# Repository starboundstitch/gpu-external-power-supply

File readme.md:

# GPU External Power Supply

The GPU External Power Supply is a project that aims to replace any computer graphics cards' power delivery system with a completely custom board. This repository contains all code, firmware, and schematics required to build the card as well as documentation on how it works.

The sister repository [geps-app](https://github.com/starboundstitch/geps-app) contains the code for the GUI application.

## Summary

The External GPU Power Card is a designed to seamlessly integrate with existing GPUs. It works by replacing the Vcore and Vmem rails with new power stages that have reduced noise, an increased voltage range, and an increased maximum current which should provide additional stability and performance benefits.

The power supply also allows full control of its voltage characteristics to provide unlimited overclocking potential. The device integrates with our companion application to provide real time monitoring and adjustment using a GUI interface, allowing more informed decisions in the overclocking process to extract as much performance as possible.

<div align="center""> 
Prototype 2
</div>

<div align="center""> 
Prototype 2 is attached to a gtx 580
</div>

## Specs

* 12 Phases (10+2)
* Vcore
  * 0-2V
  * 500A Tested
  * 900A Theoretical
  * 10 Phases
* Vcore
  * 0-2.3V
  * 100A Tested
  * 180A Theoretical
  * 2 Phases

## Hardware

This section contains the KICAD project and all the associated files.

We make extensive use of hierarchy in this project and have the following schematics:
* Vcore_stage
  * Single MOSFET that connects to the VRM Controller Vcore Channel
* Vmem_stage
  * Single MOSFET that connects to the VRM Controller Vmem Channel
* VRM_Controller
  * VRM Controller with required pinouts and filtering
* 12V_Supply
  * Input filtering and connectors
* Low_Current_Supply
  * 3.3V & 5V buck converters and LED status
* Onboard_Control
  * Buttons and Display
* U_Controller
  * Microcontroller and required connectors (including USB-C)

## Firmware

This section contains all micro-controller code and is using the rust language with the [stmf4XX-hal](https://github.com/stm32-rs/stm32f4xx-hal) library.

> [!CAUTION]
> The stm32f401RE that is used does NOT have enough SRAM to run in debug mode and it will NOT flash.

The controller should automatically build and flash with:

```
cargo run --release
```

Additionally, in the future we will support flashing via USB DFU mode (instructions TBD).

## License

All the code and hardware files in this repository are licensed according to the GPLv3 in the [LICENSE](https://github.com/starboundstitch/gpu-external-power-supply/blob/master/LICENSE) file.

In addition, many of the symbols and footprints are provided by the manufacturers for use and are thus liable under the manufactures' licenses.

This project was created by [@Xunnin](https://github.com/Xunnin), [@starboundstitch](https://github.com/starboundstitch), and [@StefClef](https://github.com/StefClef).

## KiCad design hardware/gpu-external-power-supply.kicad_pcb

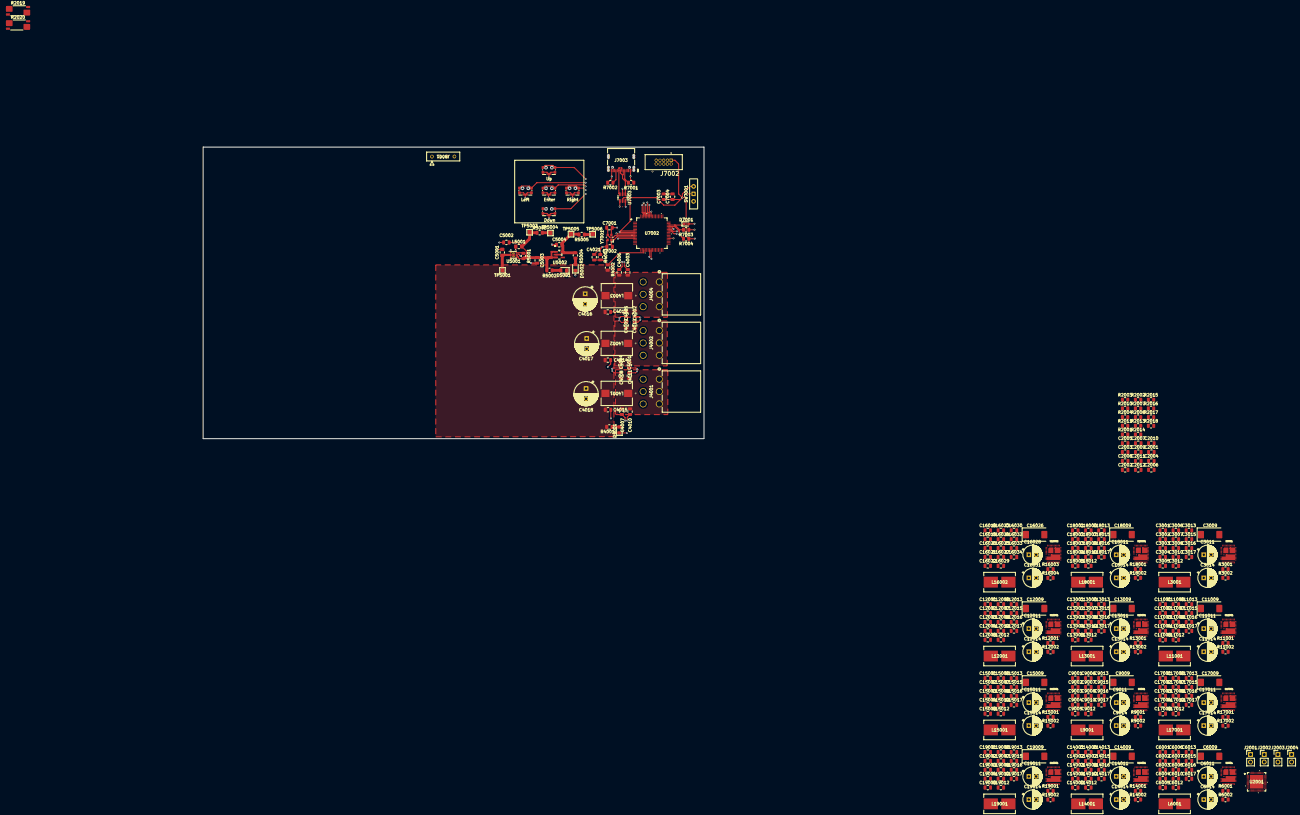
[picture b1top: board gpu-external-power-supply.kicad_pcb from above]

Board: 6 copper layers, 170.2 x 99.1 mm, 354 parts (0 on the bottom side), 141 nets.

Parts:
C2001, C2004: 1nF; C_0805_2012Metric
C2002, C2010, C2011, C2012, C5003, C5004: 1uF; C_0805_2012Metric
C2003, C2005: 100pF; C_0805_2012Metric
C2006, C3003, C3006, C3007, C3017, C6003, C6006, C6007, C6017, C9003, C9006, C9007, C9017, C11003, C11006, C11007, C11017, C12003, C12006, C12007, C12017, C13003, C13006, C13007, C13017, C14003, C14006, C14007, C14017, C15003, C15006, C15007, C15017, C16020, C16023, C16024, C16034, C17003, C17006, C17007, C17017, C18003, C18006, C18007, C18017, C19003, C19006, C19007, C19017: 0.1uF; C_0805_2012Metric
C2007, C3016, C6016, C9016, C11016, C12016, C13016, C14016, C15016, C16033, C17016, C18016, C19016: 4.7uF; C_0805_2012Metric
C2008, C2009: 2200pF; C_0805_2012Metric
C3001, C3005, C6001, C6005, C9001, C9005, C11001, C11005, C12001, C12005, C13001, C13005, C14001, C14005, C15001, C15005, C16018, C16022, C17001, C17005, C18001, C18005, C19001, C19005: 47pF; C_0805_2012Metric
C3002, C3004, C6002, C6004, C9002, C9004, C11002, C11004, C12002, C12004, C13002, C13004, C14002, C14004, C15002, C15004, C16019, C16021, C17002, C17004, C18002, C18004, C19002, C19004: 2.2uF; C_0805_2012Metric
C3008, C3010, C3012, C3015, C5002, C6008, C6010, C6012, C6015, C9008, C9010, C9012, C9015, C11008, C11010, C11012, C11015, C12008, C12010, C12012, C12015, C13008, C13010, C13012, C13015, C14008, C14010, C14012, C14015, C15008, C15010, C15012, C15015, C16025, C16027, C16029, C16032, C17008, C17010, C17012, C17015, C18008, C18010, C18012, C18015, C19008, C19010, C19012, C19015: 22uF; C_0805_2012Metric
C3009, C6009, C9009, C11009, C12009, C13009, C14009, C15009, C16026, C17009, C18009, C19009: 470uF; CP_EIA-7343-40_Kemet-Y
C3011, C3014, C6011, C6014, C9011, C9014, C11011, C11014, C12011, C12014, C13011, C13014, C14011, C14014, C15011, C15014, C16028, C16031, C17011, C17014, C18011, C18014, C19011, C19014: 220uF; CP_Radial_D6.3mm_P2.50mm
C3013, C6013, C9013, C11013, C12013, C13013, C14013, C15013, C16030, C17013, C18013, C19013: 47uF; C_0805_2012Metric
C4001, C4002, C4003: 470u; C_0805_2012Metric
C4004, C4005, C4006: 47u; C_0805_2012Metric
C4007, C4008, C4009: 10u; C_0805_2012Metric
C4010, C4011, C4012, C4021: 0.1u; C_0805_2012Metric
C4013, C4014, C4015: 330u; C_0805_2012Metric
C4016, C4017, C4018: 470u; CP_Radial_D8.0mm_P3.50mm
C5001: 10uF; C_0805_2012Metric_Pad1.18x1.45mm_HandSolder
C7001, C7002: 6pF; C_0805_2012Metric
C7003: 4.7u; C_0805_2012Metric
C7004: 100n; C_0805_2012Metric
D4001, D5001, D5002: 150080SS75000; LED_0805_2012Metric_Pad1.15x1.40mm_HandSolder
D7001: GG060303100N2P; D_0603_1608Metric
J2001, J2002, J2003, J2004: Conn_01x02_Pin; PinHeader_1x02_P2.54mm_Vertical
J4001, J4002, J4004: 353180620; CONN_35318-06xx_MOL
J7002: Conn_ARM_JTAG_SWD_10; CNC_3221-10-0100-00
J7003: USB_C_Receptacle_USB2.0_16P; 12402012E212A_AMP
J8001: Conn_01x04_Pin; CONN_PPTC041LFBN-RC_SUL
L3001, L6001, L9001, L11001, L12001, L13001, L14001, L15001, L16002, L17001, L18001, L19001: 150nH; IND_IHVR-4025JZ-3Z_VIS
L4001, L4002, L4003: 170nH; IND_IFLR4031GCERR17M01_VIS-L
L5001: 2.2uH; L_0805_2012Metric_Pad1.15x1.40mm_HandSolder
R2001, R2002, R2007, R2008, R2013, R2014, R2015, R2016, R2017, R2018, R4002: 10k; R_0805_2012Metric
R2003: 130k; R_0805_2012Metric
R2004, R2011: 37.4k; R_0805_2012Metric
R2010: 2430k; R_0805_2012Metric
R2019, R2020: 1m; R_Shunt_Vishay_WSK2512_6332Metric_T1.19mm
R3001, R6001, R9001, R11001, R12001, R13001, R14001, R15001, R16003, R17001, R18001, R19001: 2.2; R_0805_2012Metric
R3002, R6002, R9002, R11002, R12002, R13002, R14002, R15002, R16004, R17002, R18002, R19002: 0; R_0805_2012Metric
R4001: 337; R_0805_2012Metric
R4003: 3.5k; R_0805_2012Metric
R5001, R7004: 100k; R_0805_2012Metric
R5002: 100+-5; R_0805_2012Metric
R5003, R5005: 1; R_0805_2012Metric
R5004: 45+-5; R_0805_2012Metric
R7001, R7002: 5K1; R_0805_2012Metric
R7003: 10K; R_0805_2012Metric
SW7001: SW_Wuerth_450301014042; SW_Slide-03_Wuerth-WS-SLTV_10x2.5x6.4_P2.54mm
SW8001, SW8002, SW8003, SW8004, SW8005: CK_KMS2xxG; SW_SPST_CK_KMS2xxGP
TP5001: 12V -> 5V; TestPoint_Pad_1.5x1.5mm
TP5003, TP5004, TP5005, TP5006: TestPoint; TestPoint_Pad_1.5x1.5mm
U2001: TPS536C7B1RSLT; QFN48_6X6_TEX
U3001, U6001, U9001, U11001, U12001, U13001, U14001, U15001, U16002, U17001, U18001, U19001: AOZ5276QI
U5001: TPS62160DSG; WSON-8-1EP_2x2mm_P0.5mm_EP0.9x1.6mm_ThermalVias
U5002: TPS73633DBVR; DBV5
U7002: STM32C071RBT6; LQFP-64_STM
U7003: USBLC6-2SC6; SOT-23-6
Y7001: Crystal_GND24; Crystal_SMD_Abracon_ABM10-4Pin_2.5x2.0mm

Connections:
3.3V: C2006.1, C2007.1, C7003.1, C7004.1, J7002.1 (VTref), J8001.2, R2001.1, R2007.1, R2013.1, R2014.1, R2015.1, R2016.1, R2017.1, R2018.1, R5005.2, R7004.1, SW7001.3 (A), TP5006.1, U2001.47 (VCC), U7002.7 (VREF+), U7002.8 (VDD/VDDA), U7003.5 (VBUS)
5V: R5003.2, TP5004.1
12V: C4013.1, C4014.1, C4015.1, C4016.1, C4017.1, C4018.1, C5001.1, L4001.2, L4002.2, L4003.2, R4001.1, R4002.1, TP5001.1, U5001.2 (VIN), U5001.3 (EN)
12V_VOL_SENS: C4021.1, R4002.2, R4003.1, U7002.19 (PA2)
/5v: C3002.1, C6002.1, C9002.1, C11002.1, C12002.1, C13002.1, C14002.1, C15002.1, C16019.1, C17002.1, C18002.1, C19002.1, R3001.1, R6001.1, R9001.1, R11001.1, R12001.1, R13001.1, R14001.1, R15001.1, R16003.1, R17001.1, R18001.1, R19001.1, U3001.4 (PVCC), U3001.35 (EN), U6001.4 (PVCC), U6001.35 (EN), U9001.4 (PVCC), U9001.35 (EN), U11001.4 (PVCC), U11001.35 (EN), U12001.4 (PVCC), U12001.35 (EN), U13001.4 (PVCC), U13001.35 (EN), U14001.4 (PVCC), U14001.35 (EN), U15001.4 (PVCC), U15001.35 (EN), U16002.4 (PVCC), U16002.35 (EN), U17001.4 (PVCC), U17001.35 (EN), U18001.4 (PVCC), U18001.35 (EN), U19001.4 (PVCC), U19001.35 (EN)
/U Controller/PF0: C7001.2, U7002.10 (PF0-OSC_IN), Y7001.3
/U Controller/PF1: C7002.2, U7002.11 (PF1-OSC_OUT), Y7001.1
/VRM Controller/ADDR_CONFIG: R2010.2, R2011.1, U2001.42 (ADDR_CONFIG)
/VRM Controller/CSNIN: C2011.2, C2012.1, C3007.1, C3008.1, C3010.1, C3012.1, C3014.1, C6007.1, C6008.1, C6010.1, C6012.1, C6014.1, C9007.1, C9008.1, C9010.1, C9012.1, C9014.1, C11007.1, C11008.1, C11010.1, C11012.1, C11014.1, C12007.1, C12008.1, C12010.1, C12012.1, C12014.1, C13007.1, C13008.1, C13010.1, C13012.1, C13014.1, C14007.1, C14008.1, C14010.1, C14012.1, C14014.1, C15007.1, C15008.1, C15010.1, C15012.1, C15014.1, C16024.1, C16025.1, C16027.1, C16029.1, C16031.1, C17007.1, C17008.1, C17010.1, C17012.1, C17014.1, C18007.1, C18008.1, C18010.1, C18012.1, C18014.1, C19007.1, C19008.1, C19010.1, C19012.1, C19014.1, R2019.1, R2020.2, U2001.46 (VIN_CSNIN), U3001.25 (VIN), U3001.30 (VIN), U6001.25 (VIN), U6001.30 (VIN), U9001.25 (VIN), U9001.30 (VIN), U11001.25 (VIN), U11001.30 (VIN), U12001.25 (VIN), U12001.30 (VIN), U13001.25 (VIN), U13001.30 (VIN), U14001.25 (VIN), U14001.30 (VIN), U15001.25 (VIN), U15001.30 (VIN), U16002.25 (VIN), U16002.30 (VIN), U17001.25 (VIN), U17001.30 (VIN), U18001.25 (VIN), U18001.30 (VIN), U19001.25 (VIN), U19001.30 (VIN)
/VRM Controller/CSPIN: C2010.1, C2011.1, R2019.2, R2020.1, U2001.45 (CSPIN)
/VRM Controller/CUR_A_9: C18001.1, U2001.35 (ACSP9), U18001.38 (IMON)
/VRM Controller/Cur_A_1: C6001.1, U2001.27 (ACSP1), U6001.38 (IMON)
/VRM Controller/Cur_A_2: C11001.1, U2001.28 (ACSP2), U11001.38 (IMON)
/VRM Controller/Cur_A_3: C12001.1, U2001.29 (ACSP3), U12001.38 (IMON)
/VRM Controller/Cur_A_4: C13001.1, U2001.30 (ACSP4), U13001.38 (IMON)
/VRM Controller/Cur_A_5: C14001.1, U2001.31 (ACSP5), U14001.38 (IMON)
/VRM Controller/Cur_A_6: C15001.1, U2001.32 (ACSP6), U15001.38 (IMON)
/VRM Controller/Cur_A_7: C16018.1, U2001.33 (ACSP7), U16002.38 (IMON)
/VRM Controller/Cur_A_8: C17001.1, U2001.34 (ACSP8), U17001.38 (IMON)
/VRM Controller/Cur_A_10: C19001.1, U2001.36 (ACSP10), U19001.38 (IMON)
/VRM Controller/Cur_B_1: C3001.1, U2001.38 (BCSP1), U3001.38 (IMON)
/VRM Controller/Cur_B_2: C9001.1, U2001.37 (BCSP2), U9001.38 (IMON)
/VRM Controller/PWM_A_1: U2001.12 (APWM1), U6001.34 (PWM)
/VRM Controller/PWM_A_2: U2001.11 (APWM2), U11001.34 (PWM)
/VRM Controller/PWM_A_3: U2001.10 (APWM3), U12001.34 (PWM)
/VRM Controller/PWM_A_4: U2001.9 (APWM4), U13001.34 (PWM)
/VRM Controller/PWM_A_5: U2001.8 (APWM5), U14001.34 (PWM)
/VRM Controller/PWM_A_6: U2001.7 (APWM6), U15001.34 (PWM)
/VRM Controller/PWM_A_7: U2001.6 (APWM7), U16002.34 (PWM)
/VRM Controller/PWM_A_8: U2001.5 (APWM8), U17001.34 (PWM)
/VRM Controller/PWM_A_9: U2001.4 (APWM9), U18001.34 (PWM)
/VRM Controller/PWM_A_10: U2001.3 (APWM10), U19001.34 (PWM)
/VRM Controller/PWM_B_1: U2001.1 (BPWM1), U3001.34 (PWM)
/VRM Controller/PWM_B_2: U2001.2 (BPWM2), U9001.34 (PWM)
/VRM Controller/VBOOT_A: R2003.2, R2004.1, U2001.18 (VBOOT_CHA)
/VRM Controller/VREF: C2002.2, C3001.2, C3003.1, C6001.2, C6003.1, C9001.2, C9003.1, C11001.2, C11003.1, C12001.2, C12003.1, C13001.2, C13003.1, C14001.2, C14003.1, C15001.2, C15003.1, C16018.2, C16020.1, C17001.2, C17003.1, C18001.2, C18003.1, C19001.2, C19003.1, R2003.1, R2010.1, U2001.48 (VREF), U3001.39 (REFIN), U6001.39 (REFIN), U9001.39 (REFIN), U11001.39 (REFIN), U12001.39 (REFIN), U13001.39 (REFIN), U14001.39 (REFIN), U15001.39 (REFIN), U16002.39 (REFIN), U17001.39 (REFIN), U18001.39 (REFIN), U19001.39 (REFIN)
AVR_READY: R2015.2, U2001.16 (AVR_RDY), U7002.38 (PC6)
A_ENABLE: C2001.1, R2001.2, R2002.1, U2001.17 (AVR_EN), U7002.49 (PC9)
B_ENABLE: C2004.1, R2007.2, R2008.1, U2001.19 (BVR_EN_/_RESET#_/_SYNC), U7002.64 (PC10)
CORE_TEMO: C2009.1, U2001.43 (BTSEN_/_ATSEN_/_TSEN)
CORE_TEMP: C6005.1, C11005.1, C12005.1, C13005.1, C14005.1, C15005.1, C16022.1, C17005.1, C18005.1, C19005.1, U6001.36 (TMON), U11001.36 (TMON), U12001.36 (TMON), U13001.36 (TMON), U14001.36 (TMON), U15001.36 (TMON), U16002.36 (TMON), U17001.36 (TMON), U18001.36 (TMON), U19001.36 (TMON)
GND: C2001.2, C2002.1, C2004.2, C2006.2, C2007.2, C2008.2, C2009.2, C2010.2, C2012.2, C3002.2, C3003.2, C3004.2, C3005.2, C3007.2, C3008.2, C3009.2, C3010.2, C3011.2, C3012.2, C3013.2, C3014.2, C3015.2, C3016.2, C3017.2, C4001.2, C4002.2, C4003.2, C4004.2, C4005.2, C4006.2, C4007.2, C4008.2, C4009.2, C4010.2, C4011.2, C4012.2, C4013.2, C4014.2, C4015.2, C4016.2, C4017.2, C4018.2, C4021.2, C5001.2, C5002.2, C5003.2, C5004.2, C6002.2, C6003.2, C6004.2, C6005.2, C6007.2, C6008.2, C6009.2, C6010.2, C6011.2, C6012.2, C6013.2, C6014.2, C6015.2, C6016.2, C6017.2, C7001.1, C7002.1, C7003.2, C7004.2, C9002.2, C9003.2, C9004.2, C9005.2, C9007.2, C9008.2, C9009.2, C9010.2, C9011.2, C9012.2, C9013.2, C9014.2, C9015.2, C9016.2, C9017.2, C11002.2, C11003.2, C11004.2, C11005.2, C11007.2, C11008.2, C11009.2, C11010.2, C11011.2, C11012.2, C11013.2, C11014.2, C11015.2, C11016.2, C11017.2, C12002.2, C12003.2, C12004.2, C12005.2, C12007.2, C12008.2, C12009.2, C12010.2, C12011.2, C12012.2, C12013.2, C12014.2, C12015.2, C12016.2, C12017.2, C13002.2, C13003.2, C13004.2, C13005.2, C13007.2, C13008.2, C13009.2, C13010.2, C13011.2, C13012.2, C13013.2, C13014.2, C13015.2, C13016.2, C13017.2, C14002.2, C14003.2, C14004.2, C14005.2, C14007.2, C14008.2, C14009.2, C14010.2, C14011.2, C14012.2, C14013.2, C14014.2, C14015.2, C14016.2, C14017.2, C15002.2, C15003.2, C15004.2, C15005.2, C15007.2, C15008.2, C15009.2, C15010.2, C15011.2, C15012.2, C15013.2, C15014.2, C15015.2, C15016.2, C15017.2, C16019.2, C16020.2, C16021.2, C16022.2, C16024.2, C16025.2, C16026.2, C16027.2, C16028.2, C16029.2, C16030.2, C16031.2, C16032.2, C16033.2, C16034.2, C17002.2, C17003.2, C17004.2, C17005.2, C17007.2, C17008.2, C17009.2, C17010.2, C17011.2, C17012.2, C17013.2, C17014.2, C17015.2, C17016.2, C17017.2, C18002.2, C18003.2, C18004.2, C18005.2, C18007.2, C18008.2, C18009.2, C18010.2, C18011.2, C18012.2, C18013.2, C18014.2, C18015.2, C18016.2, C18017.2, C19002.2, C19003.2, C19004.2, C19005.2, C19007.2, C19008.2, C19009.2, C19010.2, C19011.2, C19012.2, C19013.2, C19014.2, C19015.2, C19016.2, C19017.2, D4001.1 (K), D5001.1 (K), D5002.1 (K), D7001.2 (A), J2002.2, J2004.2, J4001.2, J4001.4, J4001.6, J4002.2, J4002.4, J4002.6, J4004.2, J4004.4, J4004.6, J7002.3 (GND), J7002.5 (GND), J7002.9 (GNDDetect), J7003.A1 (GND), J7003.B1 (GND), J7003.S1 (SHIELD), J8001.1, R2002.2, R2004.2, R2008.2, R2011.2, R4003.2, R7001.2, R7002.2, R7003.1, SW7001.2 (C), SW8001.1, SW8001.SH (B), SW8002.1, SW8002.SH (B), SW8003.1, SW8003.SH (B), SW8004.1, SW8004.SH (B), SW8005.1, SW8005.SH (B), U2001.49 (GND), U3001.2 (AGND), U3001.5 (PGND), U3001.20 (PGND), U3001.40 (PGND), U5001.1 (PGND), U5001.4 (AGND), U5001.5 (FB), U5001.9 (PAD), U5002.2 (GND), U6001.2 (AGND), U6001.5 (PGND), U6001.20 (PGND), U6001.40 (PGND), U7002.9 (VSS/VSSA), U7003.2 (GND), U9001.2 (AGND), U9001.5 (PGND), U9001.20 (PGND), U9001.40 (PGND), U11001.2 (AGND), U11001.5 (PGND), U11001.20 (PGND), U11001.40 (PGND), U12001.2 (AGND), U12001.5 (PGND), U12001.20 (PGND), U12001.40 (PGND), U13001.2 (AGND), U13001.5 (PGND), U13001.20 (PGND), U13001.40 (PGND), U14001.2 (AGND), U14001.5 (PGND), U14001.20 (PGND), U14001.40 (PGND), U15001.2 (AGND), U15001.5 (PGND), U15001.20 (PGND), U15001.40 (PGND), U16002.2 (AGND), U16002.5 (PGND), U16002.20 (PGND), U16002.40 (PGND), U17001.2 (AGND), U17001.5 (PGND), U17001.20 (PGND), U17001.40 (PGND), U18001.2 (AGND), U18001.5 (PGND), U18001.20 (PGND), U18001.40 (PGND), U19001.2 (AGND), U19001.5 (PGND), U19001.20 (PGND), U19001.40 (PGND), Y7001.2, Y7001.4
I2C_SCL: J8001.3, U7002.24 (PA7)
I2C_SDA: J8001.4, U7002.23 (PA6)
MEM_TEMP: C2008.1, C3005.1, C9005.1, U2001.44 (ATSEN_/_BTSEN), U3001.36 (TMON), U9001.36 (TMON)
NRST: J7002.10 (~RESET), U7002.12 (PF2-NRST)
unnamed: C3006.1, R3002.2
unnamed: C3006.2, U3001.31 (PHASE), U3001.32 (PHASE)
unnamed: C4001.1, C4004.1, C4007.1, C4010.1, J4001.1, J4001.3, J4001.5, L4001.1
unnamed: C4002.1, C4005.1, C4008.1, C4011.1, J4002.1, J4002.3, J4002.5, L4002.1
unnamed: C4003.1, C4006.1, C4009.1, C4012.1, J4004.1, J4004.3, J4004.5, L4003.1
unnamed: C6006.1, R6002.2
unnamed: C6006.2, U6001.31 (PHASE), U6001.32 (PHASE)
unnamed: C9006.1, R9002.2
unnamed: C9006.2, U9001.31 (PHASE), U9001.32 (PHASE)
unnamed: C11006.1, R11002.2
unnamed: C11006.2, U11001.31 (PHASE), U11001.32 (PHASE)
unnamed: C12006.1, R12002.2
unnamed: C12006.2, U12001.31 (PHASE), U12001.32 (PHASE)
unnamed: C13006.1, R13002.2
unnamed: C13006.2, U13001.31 (PHASE), U13001.32 (PHASE)
unnamed: C14006.1, R14002.2
unnamed: C14006.2, U14001.31 (PHASE), U14001.32 (PHASE)
unnamed: C15006.1, R15002.2
unnamed: C15006.2, U15001.31 (PHASE), U15001.32 (PHASE)
unnamed: C16023.1, R16004.2
unnamed: C16023.2, U16002.31 (PHASE), U16002.32 (PHASE)
unnamed: C17006.1, R17002.2
unnamed: C17006.2, U17001.31 (PHASE), U17001.32 (PHASE)
unnamed: C18006.1, R18002.2
unnamed: C18006.2, U18001.31 (PHASE), U18001.32 (PHASE)
unnamed: C19006.1, R19002.2
unnamed: C19006.2, U19001.31 (PHASE), U19001.32 (PHASE)
unnamed: D4001.2 (A), R4001.2
unnamed: D5001.2 (A), R5002.2
unnamed: D5002.2 (A), R5004.2
unnamed: C2005.1, J2001.1, U2001.25 (AVSP)
unnamed: C2003.1, J2003.1, U2001.40 (BVSP)
unnamed: C2003.2, J2004.1, U2001.39 (BVSN)
unnamed: J7003.A5 (CC1), R7001.1
unnamed: J7003.B5 (CC2), R7002.1
unnamed: J7003.A6 (D+), J7003.B6 (D+), U7003.3 (I/O2)
unnamed: J7003.A7 (D-), J7003.B7 (D-), U7003.1 (I/O1)
unnamed: J7003.A4 (VBUS), J7003.B4 (VBUS)
unnamed: L3001.1, U3001.10 (VSWH)
unnamed: L6001.1, U6001.10 (VSWH)
unnamed: L9001.1, U9001.10 (VSWH)
unnamed: L11001.1, U11001.10 (VSWH)
unnamed: L12001.1, U12001.10 (VSWH)
unnamed: L13001.1, U13001.10 (VSWH)
unnamed: L14001.1, U14001.10 (VSWH)
unnamed: L15001.1, U15001.10 (VSWH)
unnamed: L16002.1, U16002.10 (VSWH)
unnamed: L17001.1, U17001.10 (VSWH)
unnamed: L18001.1, U18001.10 (VSWH)
unnamed: L19001.1, U19001.10 (VSWH)
unnamed: C2005.2, U2001.26 (AVSN)
unnamed: R3002.1, U3001.33 (BOOT)
unnamed: C3004.1, R3001.2, U3001.3 (VCC)
unnamed: R5001.1, U5001.8 (PG)
unnamed: L5001.1, U5001.7 (SW)
unnamed: C5002.1, C5003.1, L5001.2, R5001.2, R5002.1, R5003.1, TP5003.1, U5001.6 (VOS), U5002.1 (IN), U5002.3 (EN)
unnamed: C5004.1, R5004.1, R5005.1, TP5005.1, U5002.5 (OUT)
unnamed: R6002.1, U6001.33 (BOOT)
unnamed: C6004.1, R6001.2, U6001.3 (VCC)
unnamed: R9002.1, U9001.33 (BOOT)
unnamed: C9004.1, R9001.2, U9001.3 (VCC)
unnamed: R11002.1, U11001.33 (BOOT)
unnamed: C11004.1, R11001.2, U11001.3 (VCC)
unnamed: R12002.1, U12001.33 (BOOT)
unnamed: C12004.1, R12001.2, U12001.3 (VCC)
unnamed: R13002.1, U13001.33 (BOOT)
unnamed: C13004.1, R13001.2, U13001.3 (VCC)
unnamed: R14002.1, U14001.33 (BOOT)
unnamed: C14004.1, R14001.2, U14001.3 (VCC)
unnamed: R15002.1, U15001.33 (BOOT)
unnamed: C15004.1, R15001.2, U15001.3 (VCC)
unnamed: R16004.1, U16002.33 (BOOT)
unnamed: C16021.1, R16003.2, U16002.3 (VCC)
unnamed: R17002.1, U17001.33 (BOOT)
unnamed: C17004.1, R17001.2, U17001.3 (VCC)
unnamed: R18002.1, U18001.33 (BOOT)
unnamed: C18004.1, R18001.2, U18001.3 (VCC)
unnamed: R19002.1, U19001.33 (BOOT)
unnamed: C19004.1, R19001.2, U19001.3 (VCC)
OB_DOWN: SW8004.2, U7002.59 (PB5)
OB_ENTER: SW8003.2, U7002.62 (PB8)
OB_LEFT: SW8001.2, U7002.60 (PB6)
OB_RIGHT: SW8005.2, U7002.61 (PB7)
OB_UP: SW8002.2, U7002.58 (PB4)
PMBUS_SCL: R2017.2, U2001.14 (SMB_CLK), U7002.37 (PA9)
PMBUS_SDA: R2016.2, U2001.13 (SMB_DIO), U7002.42 (PA10)
PMBUS_SMBA: R2018.2, U2001.15 (SMB_ALERT#), U7002.18 (PA1)
SWCLK: D7001.1 (K), J7002.2 (SWDIO/TMS), R7003.2, SW7001.1 (B), U7002.46 (PA14-BOOT0)
SWDIO: J7002.4 (SWCLK/TCK), R7004.2, U7002.45 (PA13)
SWO: J7002.6 (SWO/TDO), U7002.57 (PB3)
USB_DN: U7002.43 (PA11[PA9]), U7003.6 (I/O1)
USB_DP: U7002.44 (PA12[PA10]), U7003.4 (I/O2)
VR_FAULT: R2013.2, U2001.41 (VR_FAULT#), U7002.48 (PC8)
Vcore: C6009.1, C6011.1, C6013.1, C6015.1, C6016.1, C6017.1, C11009.1, C11011.1, C11013.1, C11015.1, C11016.1, C11017.1, C12009.1, C12011.1, C12013.1, C12015.1, C12016.1, C12017.1, C13009.1, C13011.1, C13013.1, C13015.1, C13016.1, C13017.1, C14009.1, C14011.1, C14013.1, C14015.1, C14016.1, C14017.1, C15009.1, C15011.1, C15013.1, C15015.1, C15016.1, C15017.1, C16026.1, C16028.1, C16030.1, C16032.1, C16033.1, C16034.1, C17009.1, C17011.1, C17013.1, C17015.1, C17016.1, C17017.1, C18009.1, C18011.1, C18013.1, C18015.1, C18016.1, C18017.1, C19009.1, C19011.1, C19013.1, C19015.1, C19016.1, C19017.1, J2001.2, L6001.2, L11001.2, L12001.2, L13001.2, L14001.2, L15001.2, L16002.2, L17001.2, L18001.2, L19001.2, U6001.1 (VOS), U11001.1 (VOS), U12001.1 (VOS), U13001.1 (VOS), U14001.1 (VOS), U15001.1 (VOS), U16002.1 (VOS), U17001.1 (VOS), U18001.1 (VOS), U19001.1 (VOS)
Vmem: C3009.1, C3011.1, C3013.1, C3015.1, C3016.1, C3017.1, C9009.1, C9011.1, C9013.1, C9015.1, C9016.1, C9017.1, J2003.2, L3001.2, L9001.2, U3001.1 (VOS), U9001.1 (VOS)

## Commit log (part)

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2024-12-07 feat!: add hierarchal sheets for pcb
    Adds hierarchal sheets for the kicad project. This should allow easier
    collaborative editing.
2024-12-07 fix: update gitignore
2024-12-07 feat: microcontroller on the PCB
    Added the microcontroller and made some basic connections
2024-12-07 feat: button input initial
    Added initial design for buttons on the PCB
2025-01-09 feat: NCP81610 and AOZ5276QI Symbols Added
2025-01-09 feat: Laid-out MOSFET ICs
2025-01-09 feat(12V): PCIe connectors, bypass caps, clamping diode circuit
    Draft 1
2025-01-09 chore: redirect sub-schematic from untitled to Double_Mos
2025-01-09 fix: minor updates
2025-01-13 feat: add STM32C071RB symbols and footprints
2025-01-13 feat: USB-C Port and init of stm32c071
2025-01-13 feat(schematic): Boot Mode Configuration
2025-01-13 chore(schematic): Update references
2025-01-13 feat(schematic): initial 12v design
2025-01-13 feat(schematic): initial low current supply
2025-01-13 Revert "chore(schematic): Update references"
    This reverts commit 2cda2d22061e90f93ddb38c43ecf32892cd7b43c.
2025-01-15 chore(schematic): Global Labels and Boot Mode Slider
2025-01-15 feat(schematic): Added Hall Sensor
2025-01-15 chore: remove unecessary file
2025-01-15 chore: update gitignore
2025-01-15 chore: update project references
2025-01-15 feat: new pwm controller symbol
2025-01-15 feat(schematic): USB-C data line OVP
2025-01-15 refactor(schematic): proper pin mappings
2025-01-15 refactor(schematic): onboard control connect to microcontroller
2025-01-16 feat(schematic): SWD connector
2025-01-16 feat(pcb): add manufacturing constraints
2025-01-16 chore(schematic): add footprints and datasheets for microcontroller
2025-01-16 chore(pcb): default text size
2025-01-16 feat(pcb): onboard control grid
2025-01-16 chore(footprints): add connectors
2025-01-17 feat(schematic): 3.3V global label
2025-01-17 chore: add display connector
2025-01-17 feat(pcb): microcontroller and onboard control initial design
2025-01-17 feat(schematic): VRM Controller Design
    - 12v Current Sense
    - Digital I/O
    - MOSFET I/0
    - etc
2025-01-17 feat(schematic): set PMBUS address and channel A starting voltage
2025-01-17 chore(schematic): add global pins
2025-01-18 AOZ5276QI Footprint drafted and ready for use
2025-01-20 feat(12v): add correct sensor
2025-01-20 fix(schematic): 12V Supply & Low Current Supply
    Added proper switching 5V and linear 3.3V ICs.
2025-01-20 feat(schematic): 12V and Low Current
    Final changes: Added test points and assigned all footprints.
2025-01-21 feat(schematic): 12v supply footprints
2025-01-21 feat(PCB): 12V supply layout
2025-01-21 fix(schematic): Minor Style changes to u controller and onboard control
2025-01-21 chore: update annotations
2025-01-21 feat(PCB): low-current-supply layout
2025-01-21 rebase(schematic): Updated Vcore and Vmem pins
2025-01-21 feet(schematic): Vcore schematic made
2025-01-21 feat: add footprint for VRM Controller
2025-01-21 feat(schematic): Vmem schematic completed, connected controler and stages on main
2025-01-26 feat(PCB): Vrms for mem and core layed out
2025-01-29 chore(footprint): add all missing footprints
2025-01-29 chore(symbol): update missing symbols
2025-01-29 feat(PCB): fix all DRC errors
2025-01-29 chore(PCB): update constraints
2025-01-29 feat(PCB): final prototype 1 changes
2025-02-13 feat(firmware): initial blinkey program
2025-02-13 chore: update gitignore for rust files
2025-02-13 fix: stm32c071rb memory mappings
2025-02-13 feat: display init
    Initializes the ssd1306 OLED display and writes a text string to it.
    This is using I2C channel 2 and should be correct based on the hardware
    design.
2025-02-23 feat(firmware): boot_clear program
    Clears the boot_select pin on the stm32 microcontroller which allows
    entering DFU mode when asserting the boot0 pin.
2025-02-23 chore(firmware): refactor includes
2025-02-23 chore(firmware): switch to semihosting panic
2025-02-23 feat(firmware): VRM controller pin initialization
2025-02-25 chore(firmware): change text size
2025-02-25 feat(firmware): clear_display
    Clears display
2025-02-25 feat(firmware): periodic UI updates every 50ms
2025-02-25 feat(firmware): non-blocking LED Timer
    The led timer now uses a non-blocking timer algorithm such that it can
    run in the background and not delay the execution of the program.
2025-02-25 feat(firmware): inital button implementation
    Implements buttons in a high-low state that update a counter and also
    have the proper pin configurations for our design.
2025-02-25 refactor(firmware): change display configuration
    Renames some of the display configuration to make more sense given the
    system and re-orders it
2025-02-25 feat(firmware): add lexical crate for number conversions
2025-02-25 feat(firmware): Display updates and fully clears with a counter
    Implements the necessary logic for one of the numerical inputs on the
    display. The displayed value is just a counter, but should be able to be
    adapted to voltage or something else easily
2025-02-25 feat(firmware): page and channel configuration for VRM controller
2025-02-25 feat!(firmware): initial VRM controller I2C init
    Adds the traits and implementations for the basic VRM controller
    implementation so that it can be expanded upon in the future. The
    controller on the actual card is not working, but the data should be
    written properly
2025-02-25 feat(firmware): implement number of commands
2025-02-25 fix(firmware): forgor paren
2025-03-03 feat: add display_data function
    This allows displaying an arbitrary float to the display at any of the
    locations on the 'grid' where values should be written to.
2025-03-03 feat: initial UI design
    This includes the values and headers for the basic UI design of the
    microcontroller.
    Notably, it displays voltage, current, and temperature for each channel
    in a grid as well as the 'vcore', 'vmem', and unit headers.
2025-03-06 feat: point translation between value grid and pixel grid
2025-03-06 feat: mode struct and impl
    This is for the different modes that the UI can be in. Currently, there
    is a navigation mode for when the user can navigate between the values
    and an update mode so that the user can change the value that is being
    hovered over.
2025-03-06 feat: navigation struct
    This stores the current position of the user in the UI as well as
    updates the position. This means that all the position math and error
    checking is handled here and thus is easy to call from other parts in
    the code.
2025-03-06 feat: device struct
    This stores the device state including both channels in the
    microcontroller.
2025-03-06 feat: create new structs
    Adds the device and navigation struct to the code
2025-03-06 feat: new drawing modes
    Need to have more drawing modes for the UI, so this adds them.
2025-03-06 feat: inverted text style
    Used for the UI when it is hovering over a box to change (it will have
    text with off pixels instead of on).
2025-03-06 feat: UI navigation
    This allows proper navigation in the UI.
2025-03-06 feat: Update mode with default to last set value
    This makes it so the value that is shown in update mode starts with the
    value that is corrently set for that field
2025-03-06 fix: stop overflow on display
2025-03-06 feat: update mode logic
    This adds the mode logic with initial update values. Will probably be
    tweaked later once actually on the device and can be properly tested
2025-03-06 feat: display all values
    Displays all the values on the screen (from the channel structs). They
    update every time the screen updates. Might remove that update logic
    once more I2C stuff is implemented cause it would in theory update every
    slingle time (hypothetically).
2025-03-06 feat: UI for selected value
    Puts a hollow box around the currently selected value in navigation mode
    and puts a solid filled box with the updated value in the update mode.
2025-03-06 chore: add float-write to lexical crate
    Should have been done a while ago, but better late than never
2025-03-11 refactor: migrate to stm32f4xx-hal
    This includes most of the migration stuff that is necessary.
    * I2C
    * Clocks
    * Timers
    It is missing some pin-reassignments though
2025-03-11 chore: update cargo.toml
2025-03-11 chore: update flashing logic
2025-03-11 feat: navigation pin mappings
2025-03-11 feat: Channel::set_temperature()
    Adds a function to set the temperature in the device channel
2025-03-11 feat: i2c read function
2025-03-12 chore: update i2c data-rate
2025-03-12 feat: read all values to display
    This is temporary and using the set values instead of actual values in a
    lot of cases because the power conversion is not currently working
2025-03-12 feat: dynamic voltage / current step size
2025-03-12 feat: write limits to vrm controller
    We can now write the limits back to the VRM controller from the
    microcontroller dynamically for the most part. Still needs the
    pmbus-types update for generating the exponent properly
2025-04-07 feat(schematic): migrate to stm32f401re
    Migrates to the stm32f401re in the schematic and pin mappings (for the
    most part)
2025-04-08 chore: remove computer control and clean global references
2025-04-09 feat(schematic): refactor main heirarchy
    This commit makes a bunch of changes to how power is delivered on the
    schematic. It also adds the probit header and the i2c output connector
    on the main page of the schematic. Lastly, it changes it so that USB
    power should work and also not power the 5V rail to the mosfet ICs.
2025-04-15 feat: fix pcb changes for 12V and low current supply
    Swapped 5V regulator, added diodes, fixed connectors and general
    placement. Changes to complete list for 12V and low current supply.
2025-04-15 chore: remove auto_saved_files
2025-04-17 feat(footprint): add display mounts
2025-04-22 feat(footprint): add OC Club Logo
2025-04-23 feat(schematic): added footprint
    Added new footprints for devices being sourced by JLCPCB
2025-04-23 feat(schematic): added cooler mounting holes
    added cooler mounting holes to schematic
    changed temp pins to read proper tempurature
    small fixes
2025-04-23 feat(pcb): condensed pcb
    changed pcb size
    updated part sizes
    condensed components
    other small changes
2025-04-25 chore: DRC violations fixed
2025-04-25 chore: final design touches
2025-04-26 chore: silkscreen changes
2025-04-26 feat(pcb): change feedback connectors to 2x2 instead of 2 1x2s
2025-04-26 feat(pcb): final final final changes
2025-05-03 feat(pcb): Prototype-2 build files
2025-05-11 chore: change default log level
2025-05-11 fix(pmbus): improper byte ordering
2025-05-11 feat(firmware): implement USB data transfer using bincode
2025-05-11 feat: refactor commands
    I really hate how this is done even now, but not exactly sure how to
    make it properly good. I think the send_write and send_read macros are
    doing too much which is making it hard to utilize. I might simplify them
    by making them only do the actual I2C comms with the intention of being
    a better command and read whatever. Anyways, I've spent too much time on
    this and really need to finish other things right now
2025-05-11 chore: finish device channel implementation
    This makes the naming convention much less confusing. That's its main
    point.
2025-05-11 revert(b80a97c0): prototype build files
2025-05-11 chore: add LICENSE
2025-05-16 feat: display support stl
    This is the support column that goes on all 4 corners of the display to
    hold it in place so it does not get broken off or wiggle.
2025-05-16 chore(schematic): add datasheets for diodes
2025-05-17 chore: migrate pins to prototype-2
2025-05-17 feat: add vout_max and vout_min commands
2025-05-17 fix: reverse the buffer
    Forgot to include this in the other changes to write stuff
2025-05-17 chore: migrate probe-rs to onboard chip
2025-05-18 fix: move serial write behind usb polling
2025-05-18 fix: forgot to add ReadReady import
2025-05-18 fix: wrong channel for iout_oc_fault_limit
2025-05-19 fix: load setpoint and limit when in edit mode
2025-05-19 fix: disable minimum output voltage
2026-01-02 feat: update readme
2026-01-03 readme update
    added pictures to readme
